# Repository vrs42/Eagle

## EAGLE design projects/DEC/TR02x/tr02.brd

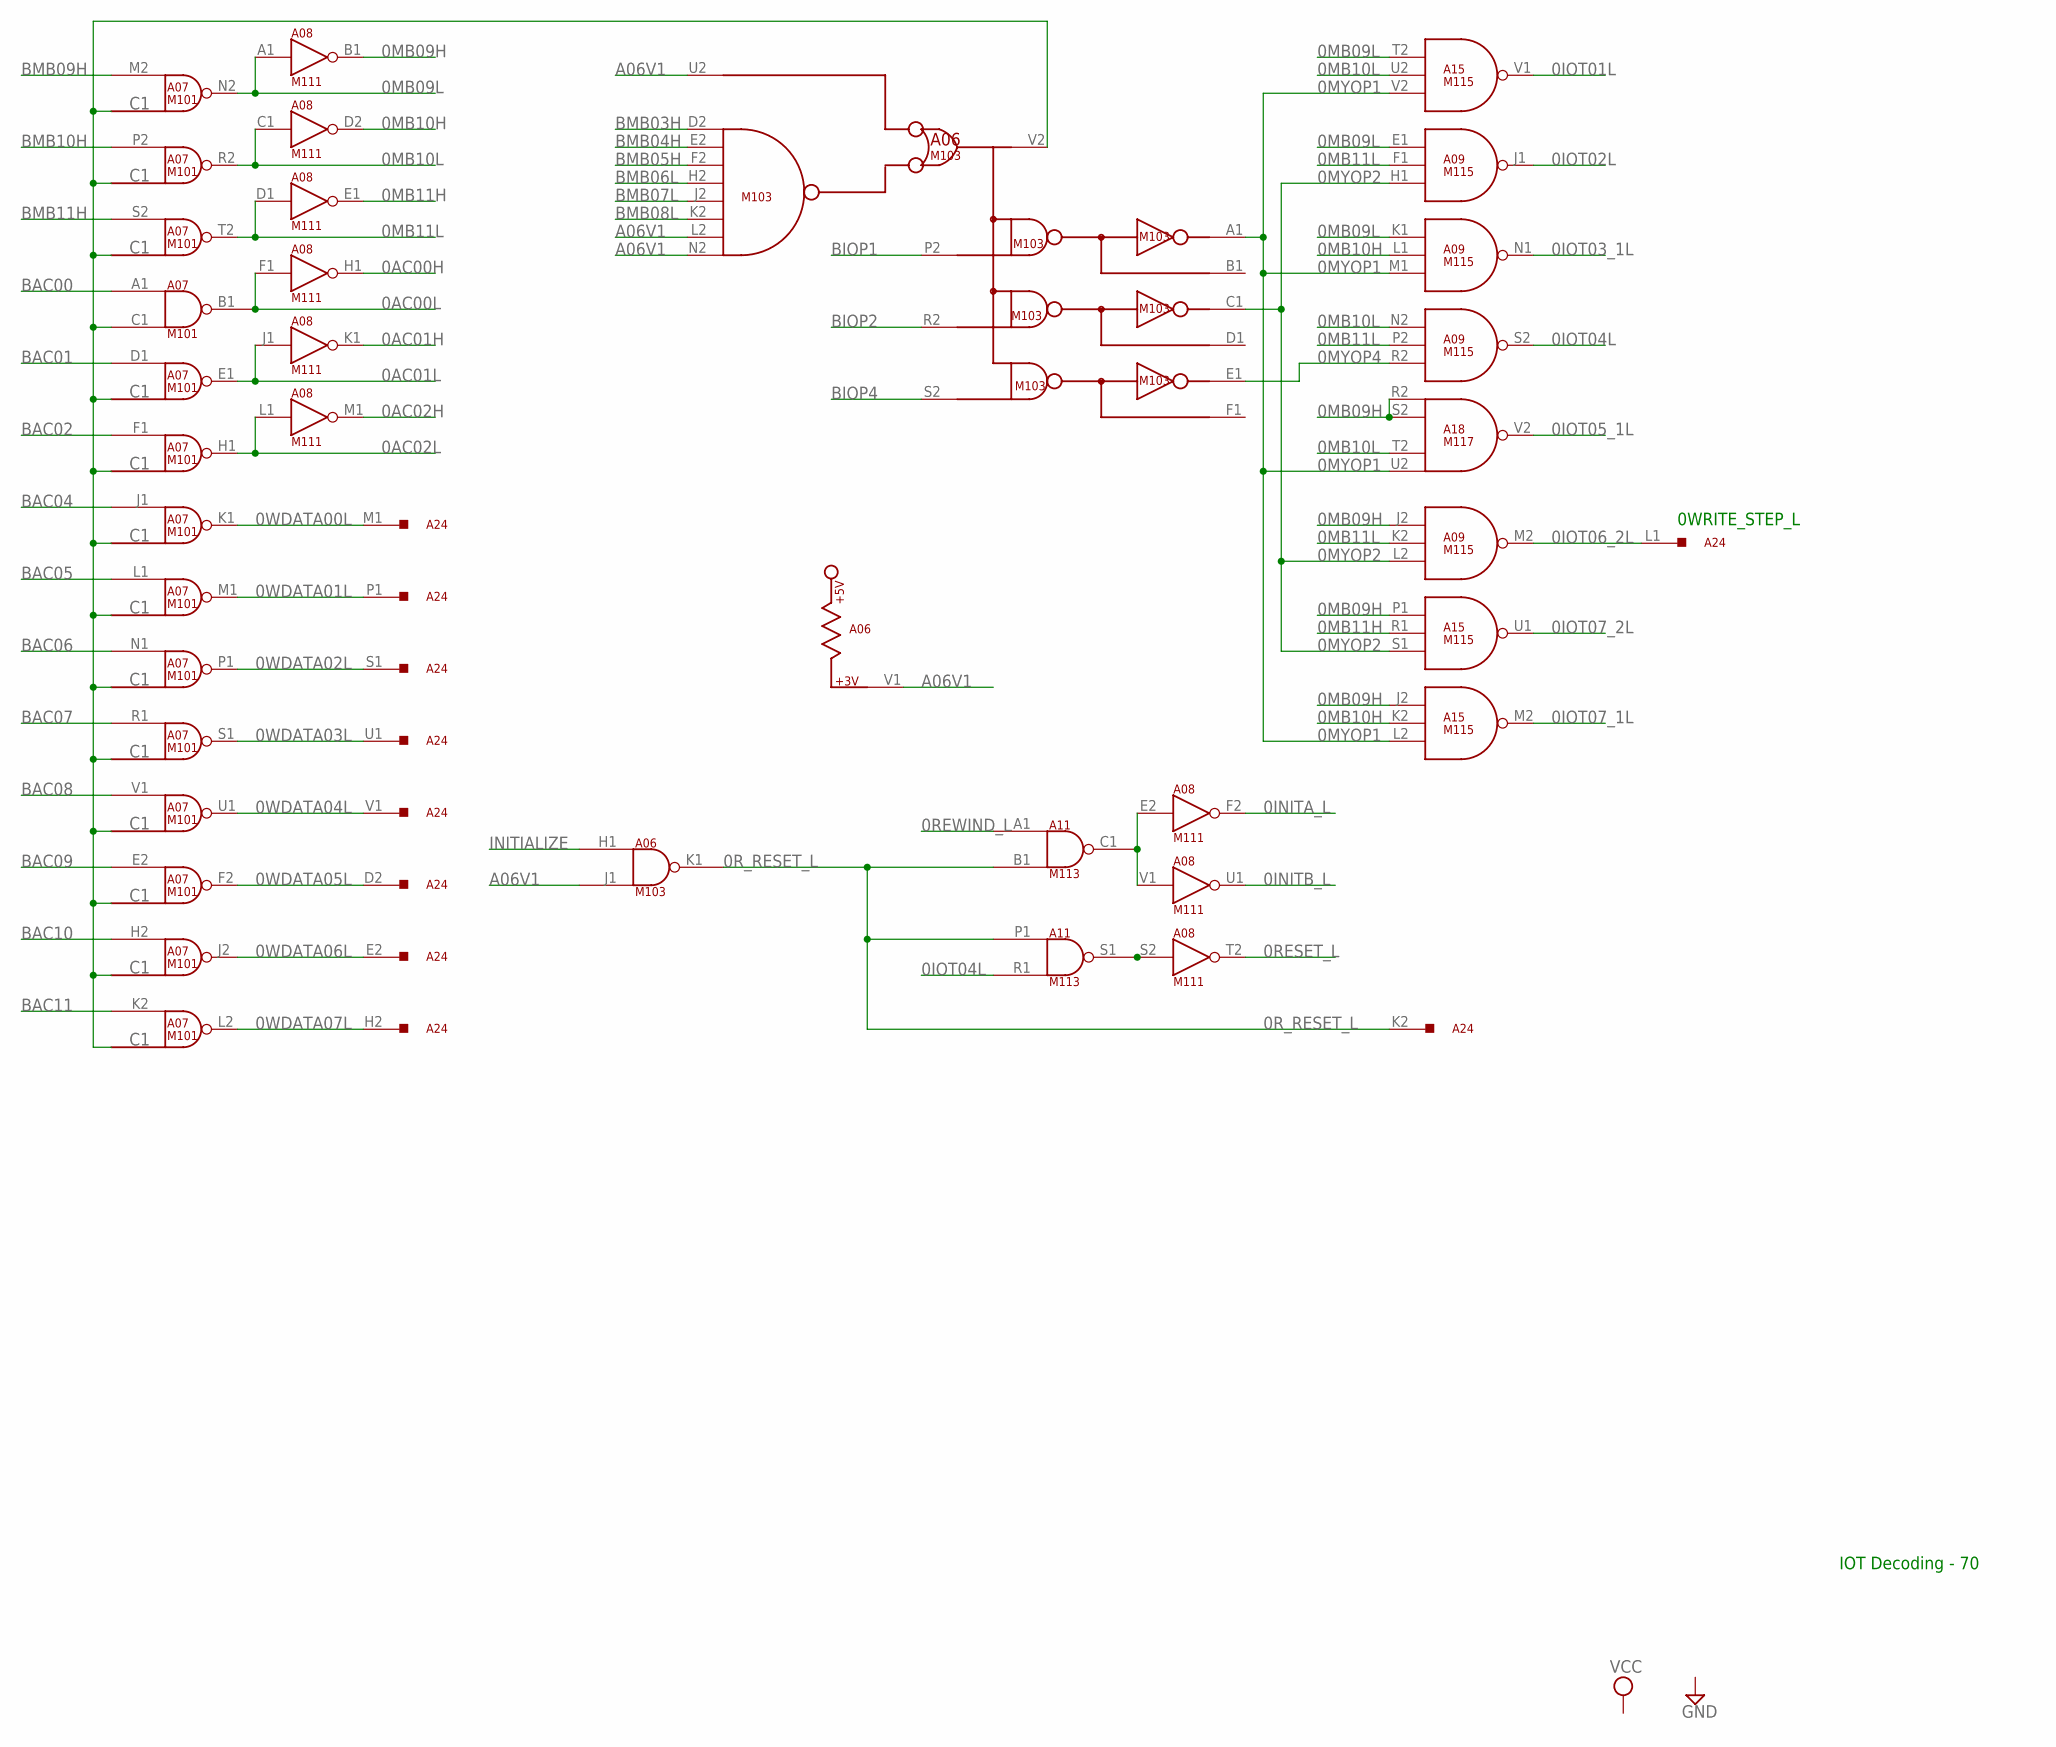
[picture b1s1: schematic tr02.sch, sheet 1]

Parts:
A06: M103; H807
A07: M101; H807
A08: M111; H807
A09, A15: M115; H807
A11: M113; H807
A18: M117; H807
A24: G784; H807

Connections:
0AC00H: A08.H1 (OUT); also elsewhere on the board
0AC00L: A07.B1 (OUT), A08.F1 (IN); also elsewhere on the board
0AC01H: A08.K1 (OUT); also elsewhere on the board
0AC01L: A07.E1 (OUT), A08.J1 (IN); also elsewhere on the board
0AC02H: A08.M1 (OUT); also elsewhere on the board
0AC02L: A07.H1 (OUT), A08.L1 (IN); also elsewhere on the board
0INITA_L: A08.F2 (OUT); also elsewhere on the board
0INITB_L: A08.U1 (OUT); also elsewhere on the board
0IOT01L: A15.V1 (OUT); also elsewhere on the board
0IOT02L: A09.J1 (OUT); also elsewhere on the board
0IOT03_1L: A09.N1 (OUT); also elsewhere on the board
0IOT04L: A09.S2 (OUT), A11.R1 (IN2); also elsewhere on the board
0IOT05_1L: A18.V2 (OUT); also elsewhere on the board
0IOT06_2L: A09.M2 (OUT), A24.L1
0IOT07_1L: A15.M2 (OUT); also elsewhere on the board
0IOT07_2L: A15.U1 (OUT); also elsewhere on the board
0MB09H: A08.B1 (OUT), A09.J2 (IN1), A15.J2 (IN1), A15.P1 (IN1), A18.R2 (IN1), A18.S2 (IN2)
0MB09L: A07.N2 (OUT), A08.A1 (IN), A09.E1 (IN1), A09.K1 (IN1), A15.T2 (IN1)
0MB10H: A08.D2 (OUT), A09.L1 (IN2), A15.K2 (IN2)
0MB10L: A07.R2 (OUT), A08.C1 (IN), A09.N2 (IN1), A15.U2 (IN2), A18.T2 (IN3)
0MB11H: A08.E1 (OUT), A15.R1 (IN2)
0MB11L: A07.T2 (OUT), A08.D1 (IN), A09.F1 (IN2), A09.K2 (IN2), A09.P2 (IN2)
0MYOP1: A06.A1, A09.M1 (IN3), A15.L2 (IN3), A15.V2 (IN3), A18.U2 (IN4)
0MYOP2: A06.C1, A09.H1 (IN3), A09.L2 (IN3), A15.S1 (IN3)
0MYOP4: A06.E1, A09.R2 (IN3)
0RESET_L: A08.T2 (OUT); also elsewhere on the board
0REWIND_L: A11.A1 (IN1); also elsewhere on the board
0R_RESET_L: A06.K1 (OUT), A11.B1 (IN2), A11.P1 (IN1), A24.K2
0WDATA00L: A07.K1 (OUT), A24.M1
0WDATA01L: A07.M1 (OUT), A24.P1
0WDATA02L: A07.P1 (OUT), A24.S1
0WDATA03L: A07.S1 (OUT), A24.U1
0WDATA04L: A07.U1 (OUT), A24.V1
0WDATA05L: A07.F2 (OUT), A24.D2
0WDATA06L: A07.J2 (OUT), A24.E2
0WDATA07L: A07.L2 (OUT), A24.H2
A06V1: A06.J1 (IN2), A06.L2, A06.N2, A06.U2, A06.V1
BAC00: A07.A1 (IN1); also elsewhere on the board
BAC01: A07.D1 (IN); also elsewhere on the board
BAC02: A07.F1 (IN); also elsewhere on the board
BAC04: A07.J1 (IN); also elsewhere on the board
BAC05: A07.L1 (IN); also elsewhere on the board
BAC06: A07.N1 (IN); also elsewhere on the board
BAC07: A07.R1 (IN); also elsewhere on the board
BAC08: A07.V1 (IN); also elsewhere on the board
BAC09: A07.E2 (IN); also elsewhere on the board
BAC10: A07.H2 (IN); also elsewhere on the board
BAC11: A07.K2 (IN); also elsewhere on the board
BIOP1: A06.P2; also elsewhere on the board
BIOP2: A06.R2; also elsewhere on the board
BIOP4: A06.S2; also elsewhere on the board
BMB03H: A06.D2; also elsewhere on the board
BMB04H: A06.E2; also elsewhere on the board
BMB05H: A06.F2; also elsewhere on the board
BMB06L: A06.H2; also elsewhere on the board
BMB07L: A06.J2; also elsewhere on the board
BMB08L: A06.K2; also elsewhere on the board
BMB09H: A07.M2 (IN); also elsewhere on the board
BMB10H: A07.P2 (IN); also elsewhere on the board
BMB11H: A07.S2 (IN); also elsewhere on the board
GND: A06.C2 (GND), A06.T1 (GND), A07.C2 (GND), A07.T1 (GND), A08.C2 (GND), A08.T1 (GND), A09.C2 (GND), A09.T1 (GND), A11.C2 (GND), A11.T1 (GND), A15.C2 (GND), A15.T1 (GND), A18.C2 (GND), A18.T1 (GND); also elsewhere on the board
INITIALIZE: A06.H1 (IN1); also elsewhere on the board
unnamed: A06.V2, A07.C1 (IN2)
unnamed: A08.S2 (IN), A11.S1 (OUT)
unnamed: A08.E2 (IN), A08.V1 (IN), A11.C1 (OUT)
VCC: A06.A2 (VCC), A07.A2 (VCC), A08.A2 (VCC), A09.A2 (VCC), A11.A2 (VCC), A15.A2 (VCC), A18.A2 (VCC); also elsewhere on the board

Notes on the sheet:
0WRITE_STEP_L
IOT Decoding - 70

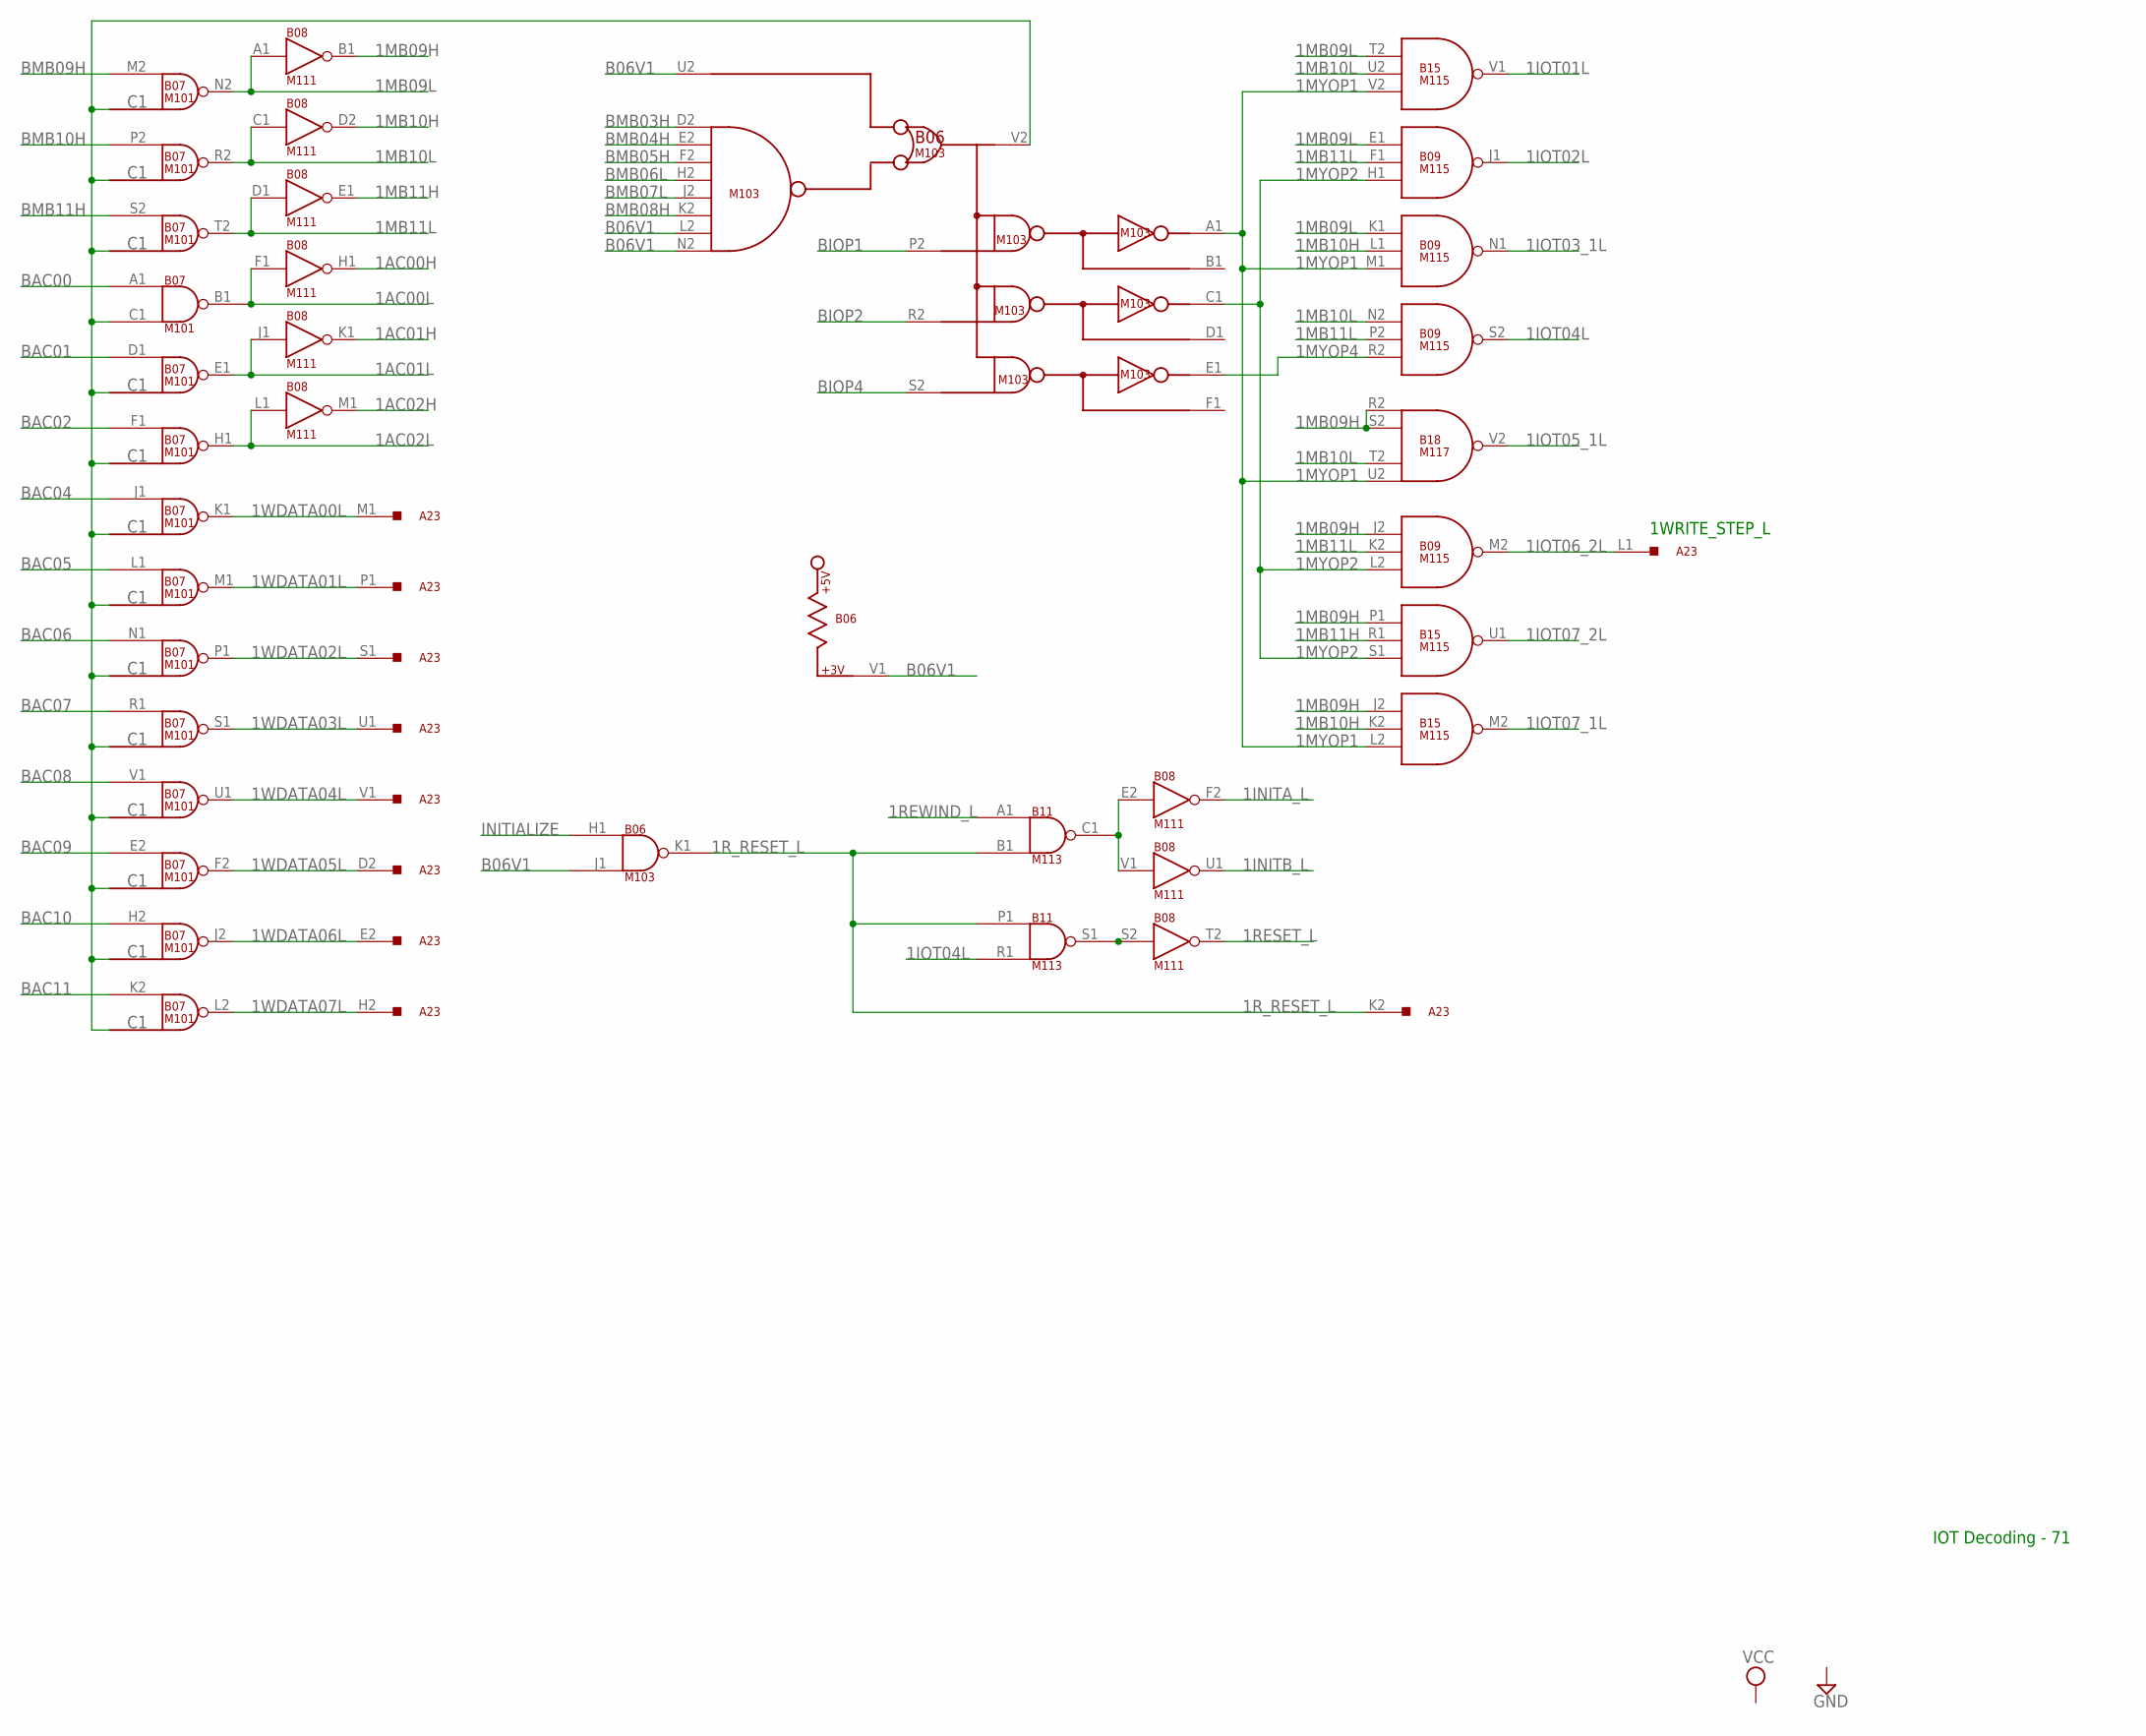
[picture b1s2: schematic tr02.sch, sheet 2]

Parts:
A23: G784; H807
B06: M103; H807
B07: M101; H807
B08: M111; H807
B09, B15: M115; H807
B11: M113; H807
B18: M117; H807

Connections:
1AC00H: B08.H1 (OUT)
1AC00L: B07.B1 (OUT), B08.F1 (IN)
1AC01H: B08.K1 (OUT)
1AC01L: B07.E1 (OUT), B08.J1 (IN)
1AC02H: B08.M1 (OUT)
1AC02L: B07.H1 (OUT), B08.L1 (IN)
1INITA_L: B08.F2 (OUT)
1INITB_L: B08.U1 (OUT)
1IOT01L: B15.V1 (OUT)
1IOT02L: B09.J1 (OUT)
1IOT03_1L: B09.N1 (OUT)
1IOT04L: B09.S2 (OUT), B11.R1 (IN2)
1IOT05_1L: B18.V2 (OUT)
1IOT06_2L: A23.L1, B09.M2 (OUT)
1IOT07_1L: B15.M2 (OUT)
1IOT07_2L: B15.U1 (OUT)
1MB09H: B08.B1 (OUT), B09.J2 (IN1), B15.J2 (IN1), B15.P1 (IN1), B18.R2 (IN1), B18.S2 (IN2)
1MB09L: B07.N2 (OUT), B08.A1 (IN), B09.E1 (IN1), B09.K1 (IN1), B15.T2 (IN1)
1MB10H: B08.D2 (OUT), B09.L1 (IN2), B15.K2 (IN2)
1MB10L: B07.R2 (OUT), B08.C1 (IN), B09.N2 (IN1), B15.U2 (IN2), B18.T2 (IN3)
1MB11H: B08.E1 (OUT), B15.R1 (IN2)
1MB11L: B07.T2 (OUT), B08.D1 (IN), B09.F1 (IN2), B09.K2 (IN2), B09.P2 (IN2)
1MYOP1: B06.A1, B09.M1 (IN3), B15.L2 (IN3), B15.V2 (IN3), B18.U2 (IN4)
1MYOP2: B06.C1, B09.H1 (IN3), B09.L2 (IN3), B15.S1 (IN3)
1MYOP4: B06.E1, B09.R2 (IN3)
1RESET_L: B08.T2 (OUT)
1REWIND_L: B11.A1 (IN1)
1R_RESET_L: A23.K2, B06.K1 (OUT), B11.B1 (IN2), B11.P1 (IN1)
1WDATA00L: A23.M1, B07.K1 (OUT)
1WDATA01L: A23.P1, B07.M1 (OUT)
1WDATA02L: A23.S1, B07.P1 (OUT)
1WDATA03L: A23.U1, B07.S1 (OUT)
1WDATA04L: A23.V1, B07.U1 (OUT)
1WDATA05L: A23.D2, B07.F2 (OUT)
1WDATA06L: A23.E2, B07.J2 (OUT)
1WDATA07L: A23.H2, B07.L2 (OUT)
B06V1: B06.J1 (IN2), B06.L2, B06.N2, B06.U2, B06.V1
BAC00: B07.A1 (IN1); also elsewhere on the board
BAC01: B07.D1 (IN); also elsewhere on the board
BAC02: B07.F1 (IN); also elsewhere on the board
BAC04: B07.J1 (IN); also elsewhere on the board
BAC05: B07.L1 (IN); also elsewhere on the board
BAC06: B07.N1 (IN); also elsewhere on the board
BAC07: B07.R1 (IN); also elsewhere on the board
BAC08: B07.V1 (IN); also elsewhere on the board
BAC09: B07.E2 (IN); also elsewhere on the board
BAC10: B07.H2 (IN); also elsewhere on the board
BAC11: B07.K2 (IN); also elsewhere on the board
BIOP1: B06.P2; also elsewhere on the board
BIOP2: B06.R2; also elsewhere on the board
BIOP4: B06.S2; also elsewhere on the board
BMB03H: B06.D2; also elsewhere on the board
BMB04H: B06.E2; also elsewhere on the board
BMB05H: B06.F2; also elsewhere on the board
BMB06L: B06.H2; also elsewhere on the board
BMB07L: B06.J2; also elsewhere on the board
BMB08H: B06.K2; also elsewhere on the board
BMB09H: B07.M2 (IN); also elsewhere on the board
BMB10H: B07.P2 (IN); also elsewhere on the board
BMB11H: B07.S2 (IN); also elsewhere on the board
GND: B06.C2 (GND), B06.T1 (GND), B07.C2 (GND), B07.T1 (GND), B08.C2 (GND), B08.T1 (GND), B09.C2 (GND), B09.T1 (GND), B11.C2 (GND), B11.T1 (GND), B15.C2 (GND), B15.T1 (GND), B18.C2 (GND), B18.T1 (GND); also elsewhere on the board
INITIALIZE: B06.H1 (IN1); also elsewhere on the board
unnamed: B06.V2, B07.C1 (IN2)
unnamed: B08.S2 (IN), B11.S1 (OUT)
unnamed: B08.E2 (IN), B08.V1 (IN), B11.C1 (OUT)
VCC: B06.A2 (VCC), B07.A2 (VCC), B08.A2 (VCC), B09.A2 (VCC), B11.A2 (VCC), B15.A2 (VCC), B18.A2 (VCC); also elsewhere on the board

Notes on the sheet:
1WRITE_STEP_L
IOT Decoding - 71

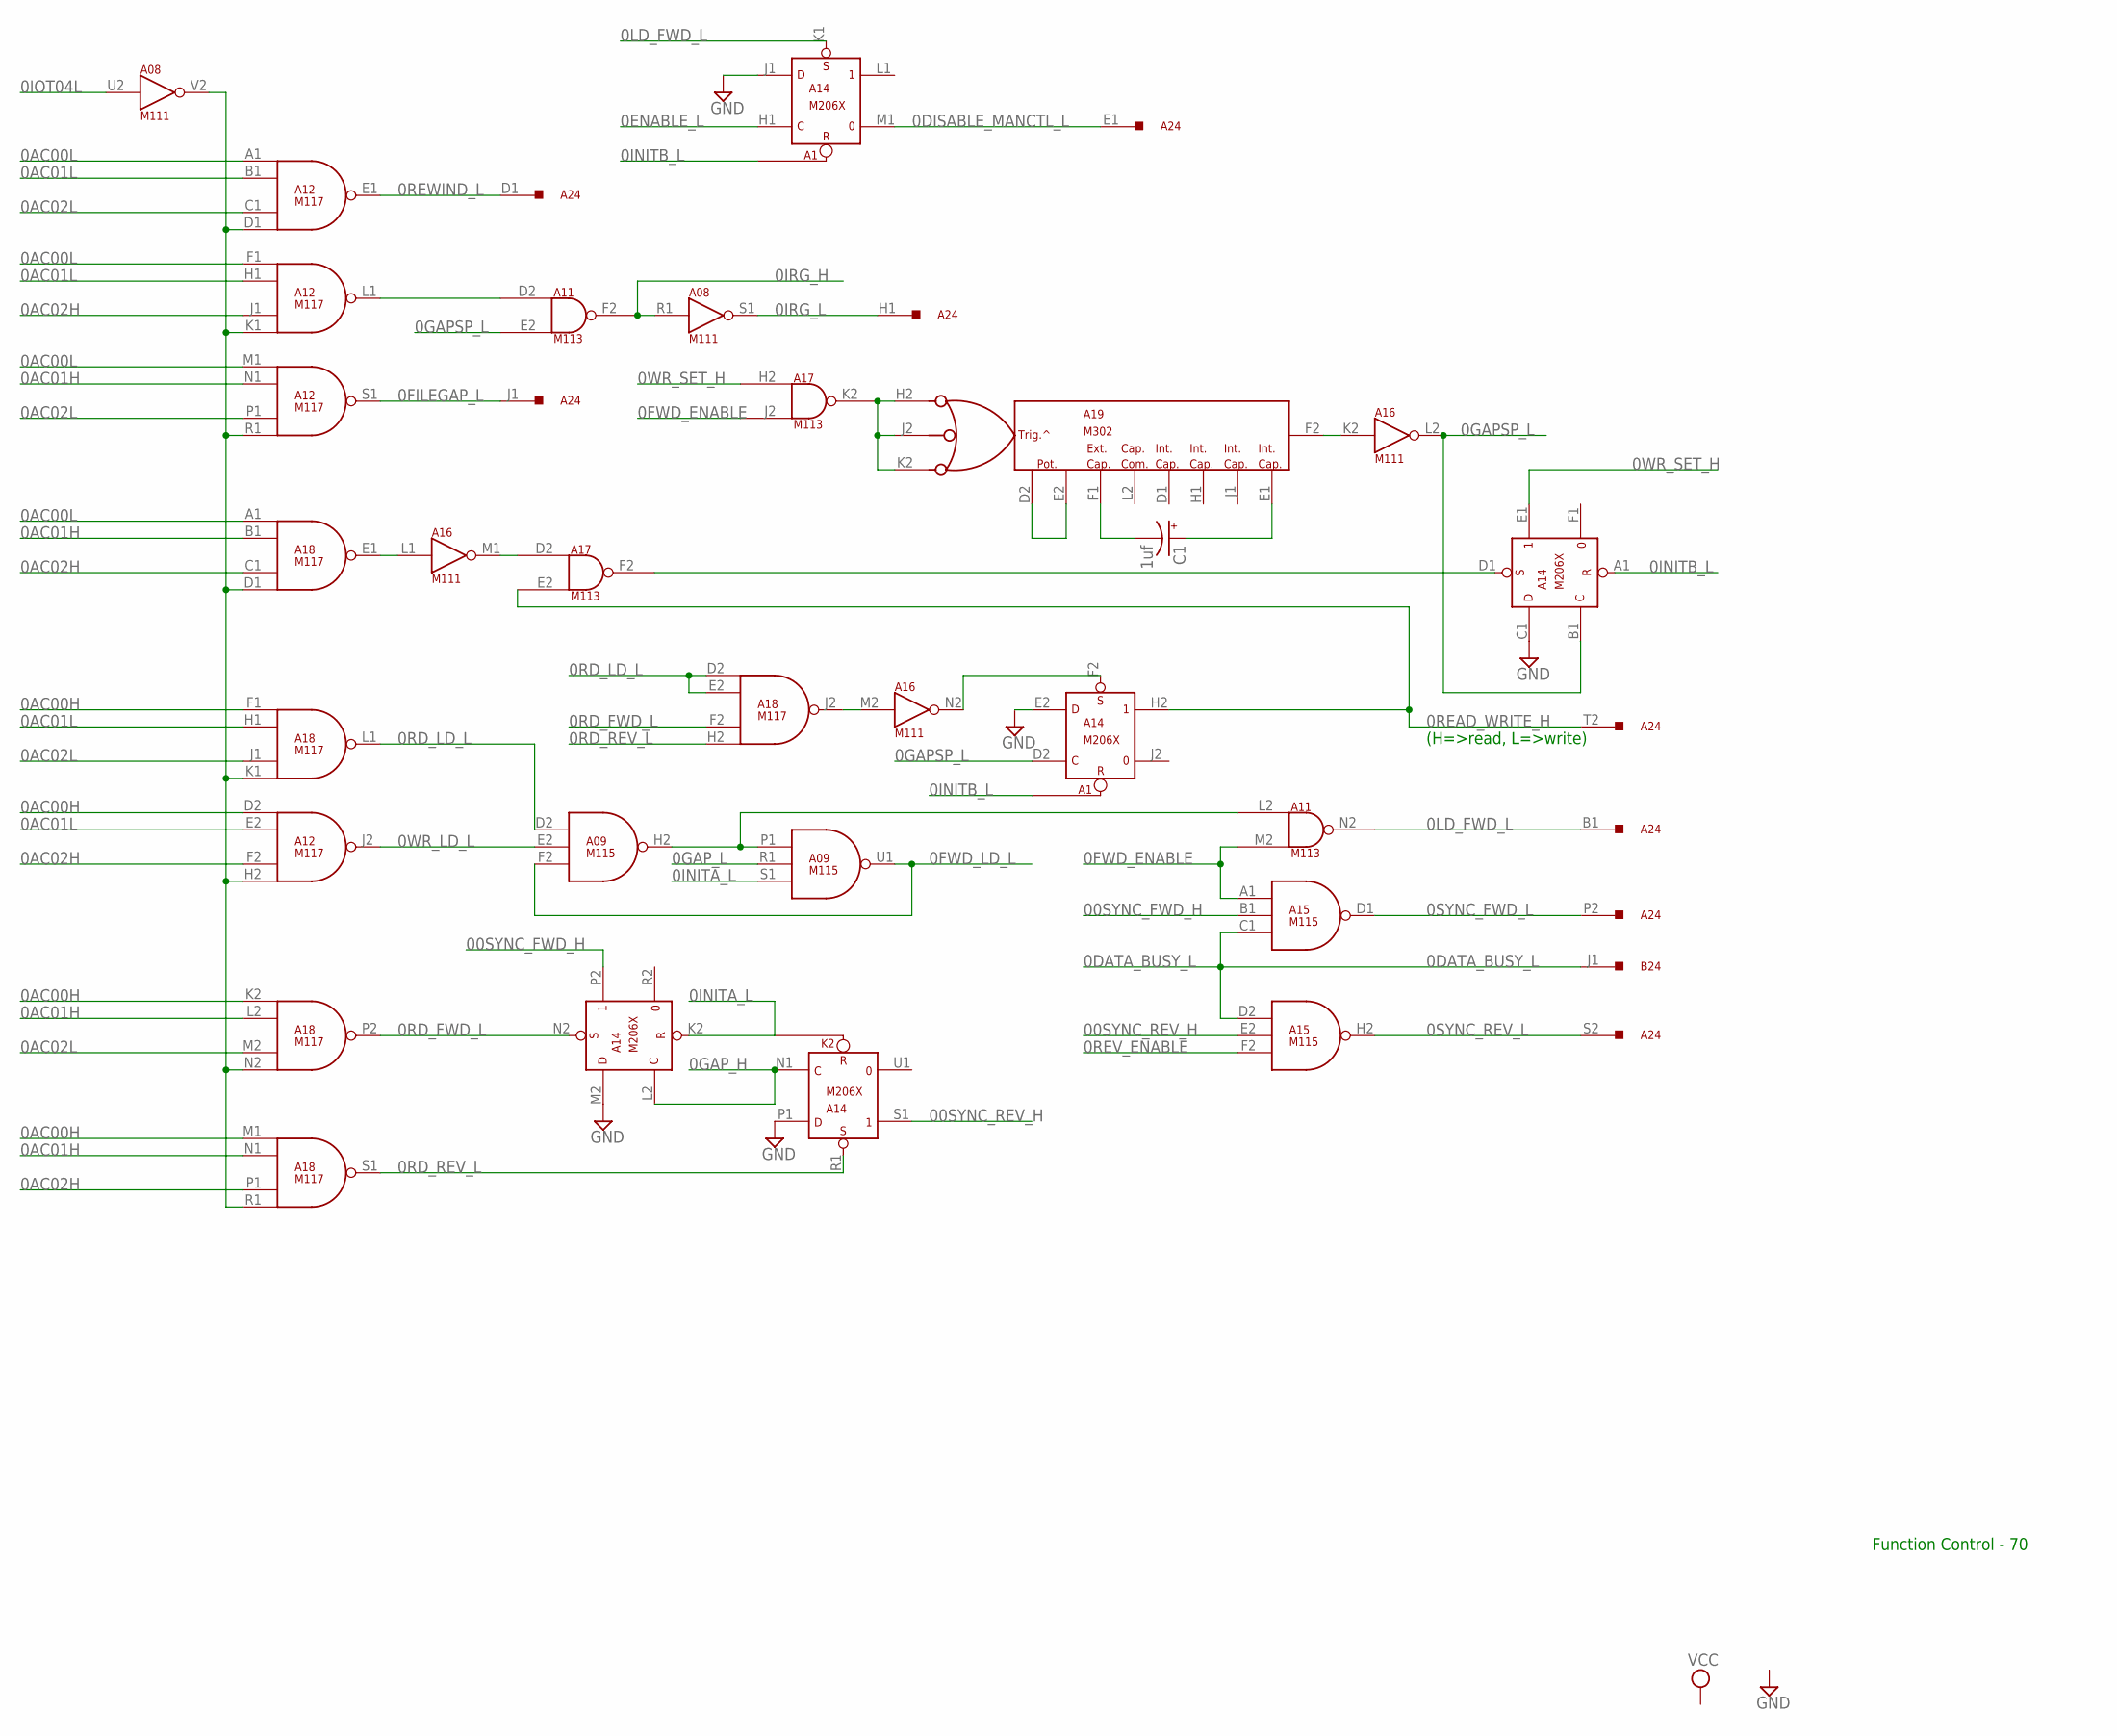
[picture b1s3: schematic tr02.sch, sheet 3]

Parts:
A08, A16: M111; H807
A09, A15: M115; H807
A11, A17: M113; H807
A12, A18: M117; H807
A14: M206X; H807
A19: M302; H807
A24: G784; H807
B24: G784; H807
C1: 1uf; E22-6

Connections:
0AC00H: A12.D2 (IN1), A18.F1 (IN1), A18.K2 (IN1), A18.M1 (IN1); also elsewhere on the board
0AC00L: A12.A1 (IN1), A12.F1 (IN1), A12.M1 (IN1), A18.A1 (IN1); also elsewhere on the board
0AC01H: A12.N1 (IN2), A18.B1 (IN2), A18.L2 (IN2), A18.N1 (IN2); also elsewhere on the board
0AC01L: A12.B1 (IN2), A12.E2 (IN2), A12.H1 (IN2), A18.H1 (IN2); also elsewhere on the board
0AC02H: A12.F2 (IN3), A12.J1 (IN3), A18.C1 (IN3), A18.P1 (IN3); also elsewhere on the board
0AC02L: A12.C1 (IN3), A12.P1 (IN3), A18.J1 (IN3), A18.M2 (IN3); also elsewhere on the board
0DATA_BUSY_L: A15.C1 (IN3), A15.D2 (IN1), B24.J1
0DISABLE_MANCTL_L: A14.M1 (0), A24.E1; also elsewhere on the board
0ENABLE_L: A14.H1 (C); also elsewhere on the board
0FILEGAP_L: A12.S1 (OUT), A24.J1
0FWD_ENABLE: A11.M2 (IN2), A15.A1 (IN1), A17.J2 (IN2); also elsewhere on the board
0FWD_LD_L: A09.F2 (IN3), A09.U1 (OUT); also elsewhere on the board
0GAPSP_L: A11.E2 (IN2), A14.B1 (C), A14.D2 (C), A16.L2 (OUT)
0GAP_H: A14.L2 (C), A14.N1 (C); also elsewhere on the board
0GAP_L: A09.R1 (IN2); also elsewhere on the board
0INITA_L: A09.S1 (IN3), A14.K2 (R); also elsewhere on the board
0INITB_L: A14.A1 (R); also elsewhere on the board
0IOT04L: A08.U2 (IN); also elsewhere on the board
0IRG_H: A08.R1 (IN), A11.F2 (OUT)
0IRG_L: A08.S1 (OUT), A24.H1; also elsewhere on the board
0LD_FWD_L: A11.N2 (OUT), A14.K1 (S), A24.B1
0RD_FWD_L: A14.N2 (S), A18.F2 (IN3), A18.P2 (OUT)
0RD_LD_L: A09.D2 (IN1), A18.D2 (IN1), A18.E2 (IN2), A18.L1 (OUT)
0RD_REV_L: A14.R1 (S), A18.H2 (IN4), A18.S1 (OUT)
0READ_WRITE_H: A14.H2 (1), A17.E2 (IN2), A24.T2; also elsewhere on the board
0REV_ENABLE: A15.F2 (IN3); also elsewhere on the board
0REWIND_L: A12.E1 (OUT), A24.D1; also elsewhere on the board
00SYNC_FWD_H: A14.P2 (1), A15.B1 (IN2)
0SYNC_FWD_L: A15.D1 (OUT), A24.P2; also elsewhere on the board
00SYNC_REV_H: A14.S1 (1), A15.E2 (IN2)
0SYNC_REV_L: A15.H2 (OUT), A24.S2; also elsewhere on the board
0WR_LD_L: A09.E2 (IN2), A12.J2 (OUT)
0WR_SET_H: A14.E1 (1), A17.H2 (IN1)
GND: A08.C2 (GND), A08.T1 (GND), A09.C2 (GND), A09.T1 (GND), A11.C2 (GND), A11.T1 (GND), A12.C2 (GND), A12.T1 (GND), A14.C1 (D), A14.C2 (GND), A14.E2 (D), A14.J1 (D), A14.M2 (D), A14.P1 (D), A14.T1 (GND), A15.C2 (GND), A15.T1 (GND), A16.C2 (GND), A16.T1 (GND), A17.C2 (GND), A17.T1 (GND), A18.C2 (GND), A18.T1 (GND), A19.C2 (GND), A19.T1 (GND); also elsewhere on the board
unnamed: A16.M1 (OUT), A17.D2 (IN1)
unnamed: A16.L1 (IN), A18.E1 (OUT)
unnamed: A17.K2 (OUT), A19.H2, A19.J2, A19.K2
unnamed: A19.F1, C1.-
unnamed: A11.D2 (IN1), A12.L1 (OUT)
unnamed: A08.V2 (OUT), A12.D1 (IN4), A12.H2 (IN4), A12.K1 (IN4), A12.R1 (IN4), A18.D1 (IN4), A18.K1 (IN4), A18.N2 (IN4), A18.R1 (IN4)
unnamed: A19.E1, C1.+
unnamed: A19.D2, A19.E2
unnamed: A16.K2 (IN), A19.F2
unnamed: A14.D1 (S), A17.F2 (OUT)
unnamed: A14.F2 (S), A16.N2 (OUT)
unnamed: A09.H2 (OUT), A09.P1 (IN1), A11.L2 (IN1)
unnamed: A16.M2 (IN), A18.J2 (OUT)
VCC: A08.A2 (VCC), A09.A2 (VCC), A11.A2 (VCC), A12.A2 (VCC), A14.A2 (VCC), A15.A2 (VCC), A16.A2 (VCC), A17.A2 (VCC), A18.A2 (VCC), A19.A2 (VCC); also elsewhere on the board

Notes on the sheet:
Function Control - 70
(H=>read, L=>write)

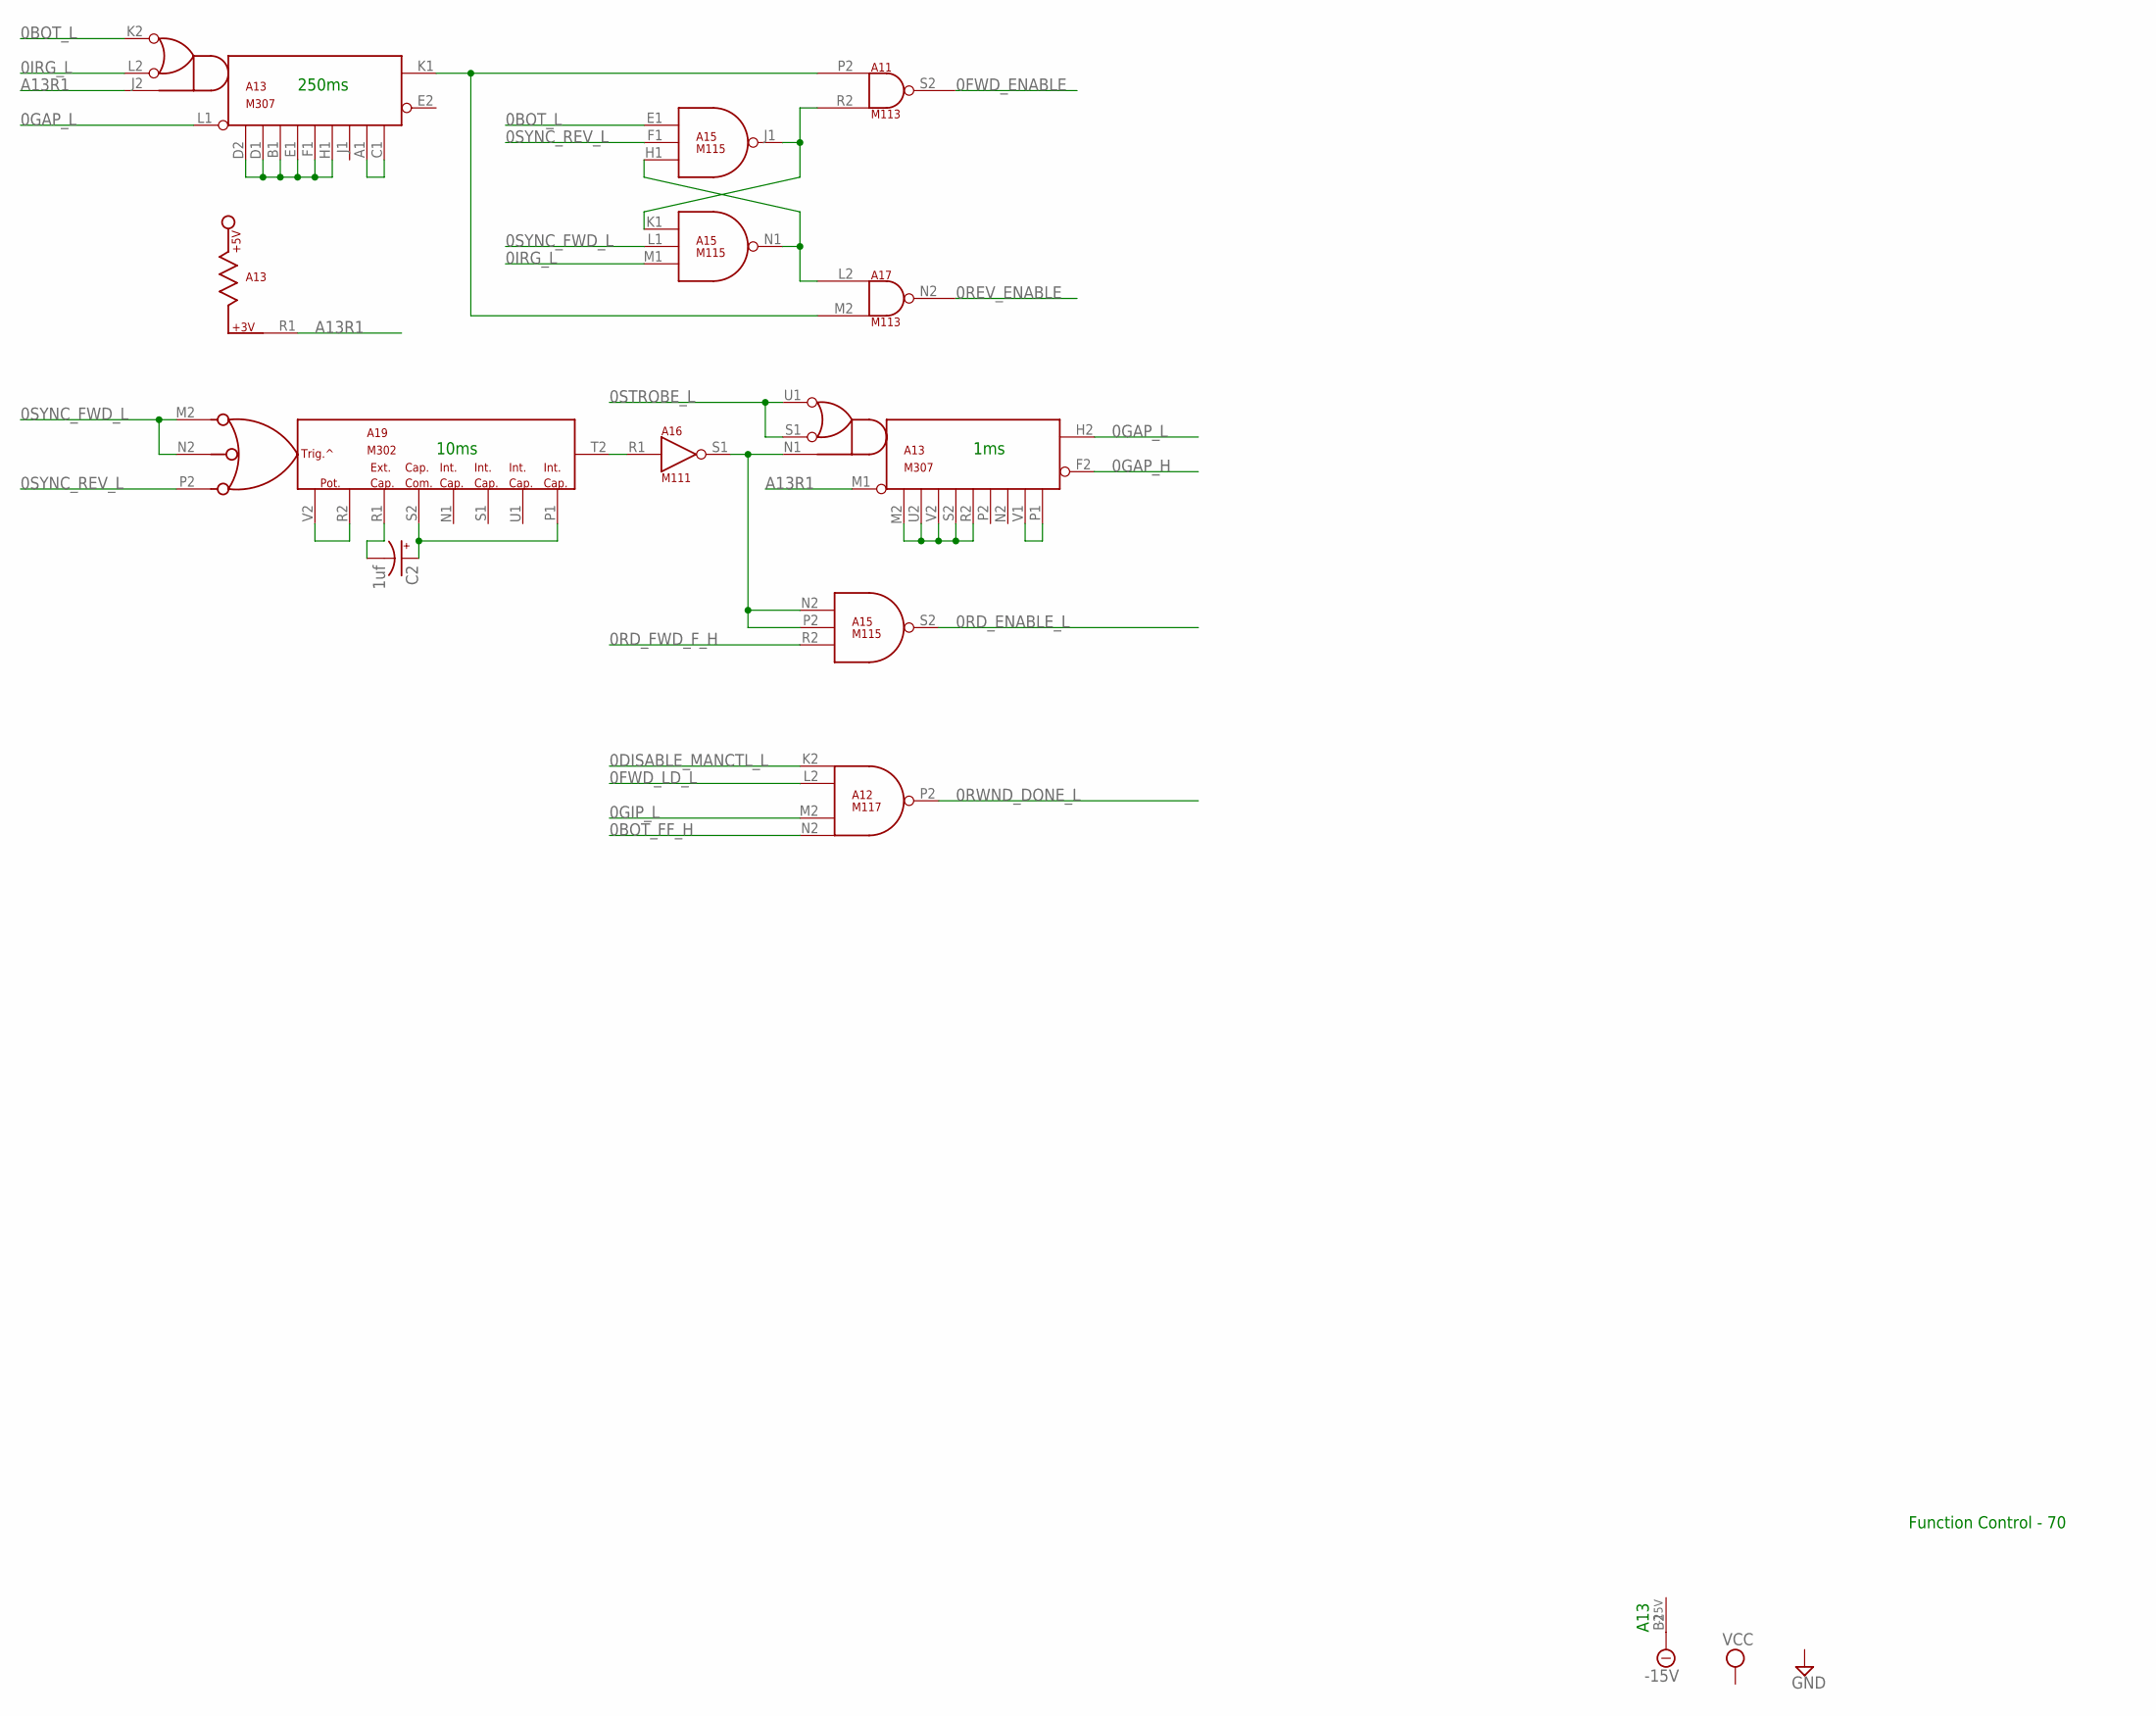
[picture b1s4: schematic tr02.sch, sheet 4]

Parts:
A11, A17: M113; H807
A12: M117; H807
A13: M307; H807
A15: M115; H807
A16: M111; H807
A19: M302; H807
C2: 1uf; E22-6

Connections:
0BOT_FF_H: A12.N2 (IN4); also elsewhere on the board
0BOT_L: A13.K2 (U1), A15.E1 (IN1); also elsewhere on the board
0DISABLE_MANCTL_L: A12.K2 (IN1); also elsewhere on the board
0FWD_ENABLE: A11.S2 (OUT); also elsewhere on the board
0FWD_LD_L: A12.L2 (IN2); also elsewhere on the board
0GAP_H: A13.F2; also elsewhere on the board
0GAP_L: A13.H2, A13.L1 (M1); also elsewhere on the board
0GIP_L: A12.M2 (IN3); also elsewhere on the board
0IRG_L: A13.L2 (S1), A15.M1 (IN3); also elsewhere on the board
0RD_ENABLE_L: A15.S2 (OUT); also elsewhere on the board
0RD_FWD_F_H: A15.R2 (IN3)
0REV_ENABLE: A17.N2 (OUT); also elsewhere on the board
0RWND_DONE_L: A12.P2 (OUT); also elsewhere on the board
0STROBE_L: A13.S1, A13.U1; also elsewhere on the board
0SYNC_FWD_L: A15.L1 (IN2), A19.M2 (H2), A19.N2 (J2); also elsewhere on the board
0SYNC_REV_L: A15.F1 (IN2), A19.P2 (K2); also elsewhere on the board
-15V: A13.B2 (-15V)
A13R1: A13.J2 (N1), A13.M1, A13.R1
GND: A11.C2 (GND), A11.T1 (GND), A12.C2 (GND), A12.T1 (GND), A13.C2 (GND), A13.T1 (GND), A15.C2 (GND), A15.T1 (GND), A16.C2 (GND), A16.T1 (GND), A17.C2 (GND), A17.T1 (GND), A19.C2 (GND), A19.T1 (GND); also elsewhere on the board
unnamed: A13.B1 (V2), A13.D1 (U2), A13.D2 (M2), A13.E1 (S2), A13.F1 (R2), A13.H1 (P2)
unnamed: A15.H1 (IN3), A15.N1 (OUT), A17.L2 (IN1)
unnamed: A13.A1 (V1), A13.C1 (P1)
unnamed: A11.P2 (IN1), A13.K1 (H2), A17.M2 (IN2)
unnamed: A11.R2 (IN2), A15.J1 (OUT), A15.K1 (IN1)
unnamed: A19.R2 (E2), A19.V2 (D2)
unnamed: A19.R1 (F1), C2.-
unnamed: A19.P1 (E1), A19.S2 (L2), C2.+
unnamed: A16.R1 (IN), A19.T2 (F2)
unnamed: A13.N1, A15.N2 (IN1), A15.P2 (IN2), A16.S1 (OUT)
unnamed: A13.M2, A13.R2, A13.S2, A13.U2, A13.V2
unnamed: A13.P1, A13.V1
VCC: A11.A2 (VCC), A12.A2 (VCC), A13.A2 (VCC), A15.A2 (VCC), A16.A2 (VCC), A17.A2 (VCC), A19.A2 (VCC); also elsewhere on the board

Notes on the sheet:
Function Control - 70
250ms
10ms
1ms
A13

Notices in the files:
projects/DEC/TSC8-75/TSC8-75.brd:
COPYRIGHT 1975
